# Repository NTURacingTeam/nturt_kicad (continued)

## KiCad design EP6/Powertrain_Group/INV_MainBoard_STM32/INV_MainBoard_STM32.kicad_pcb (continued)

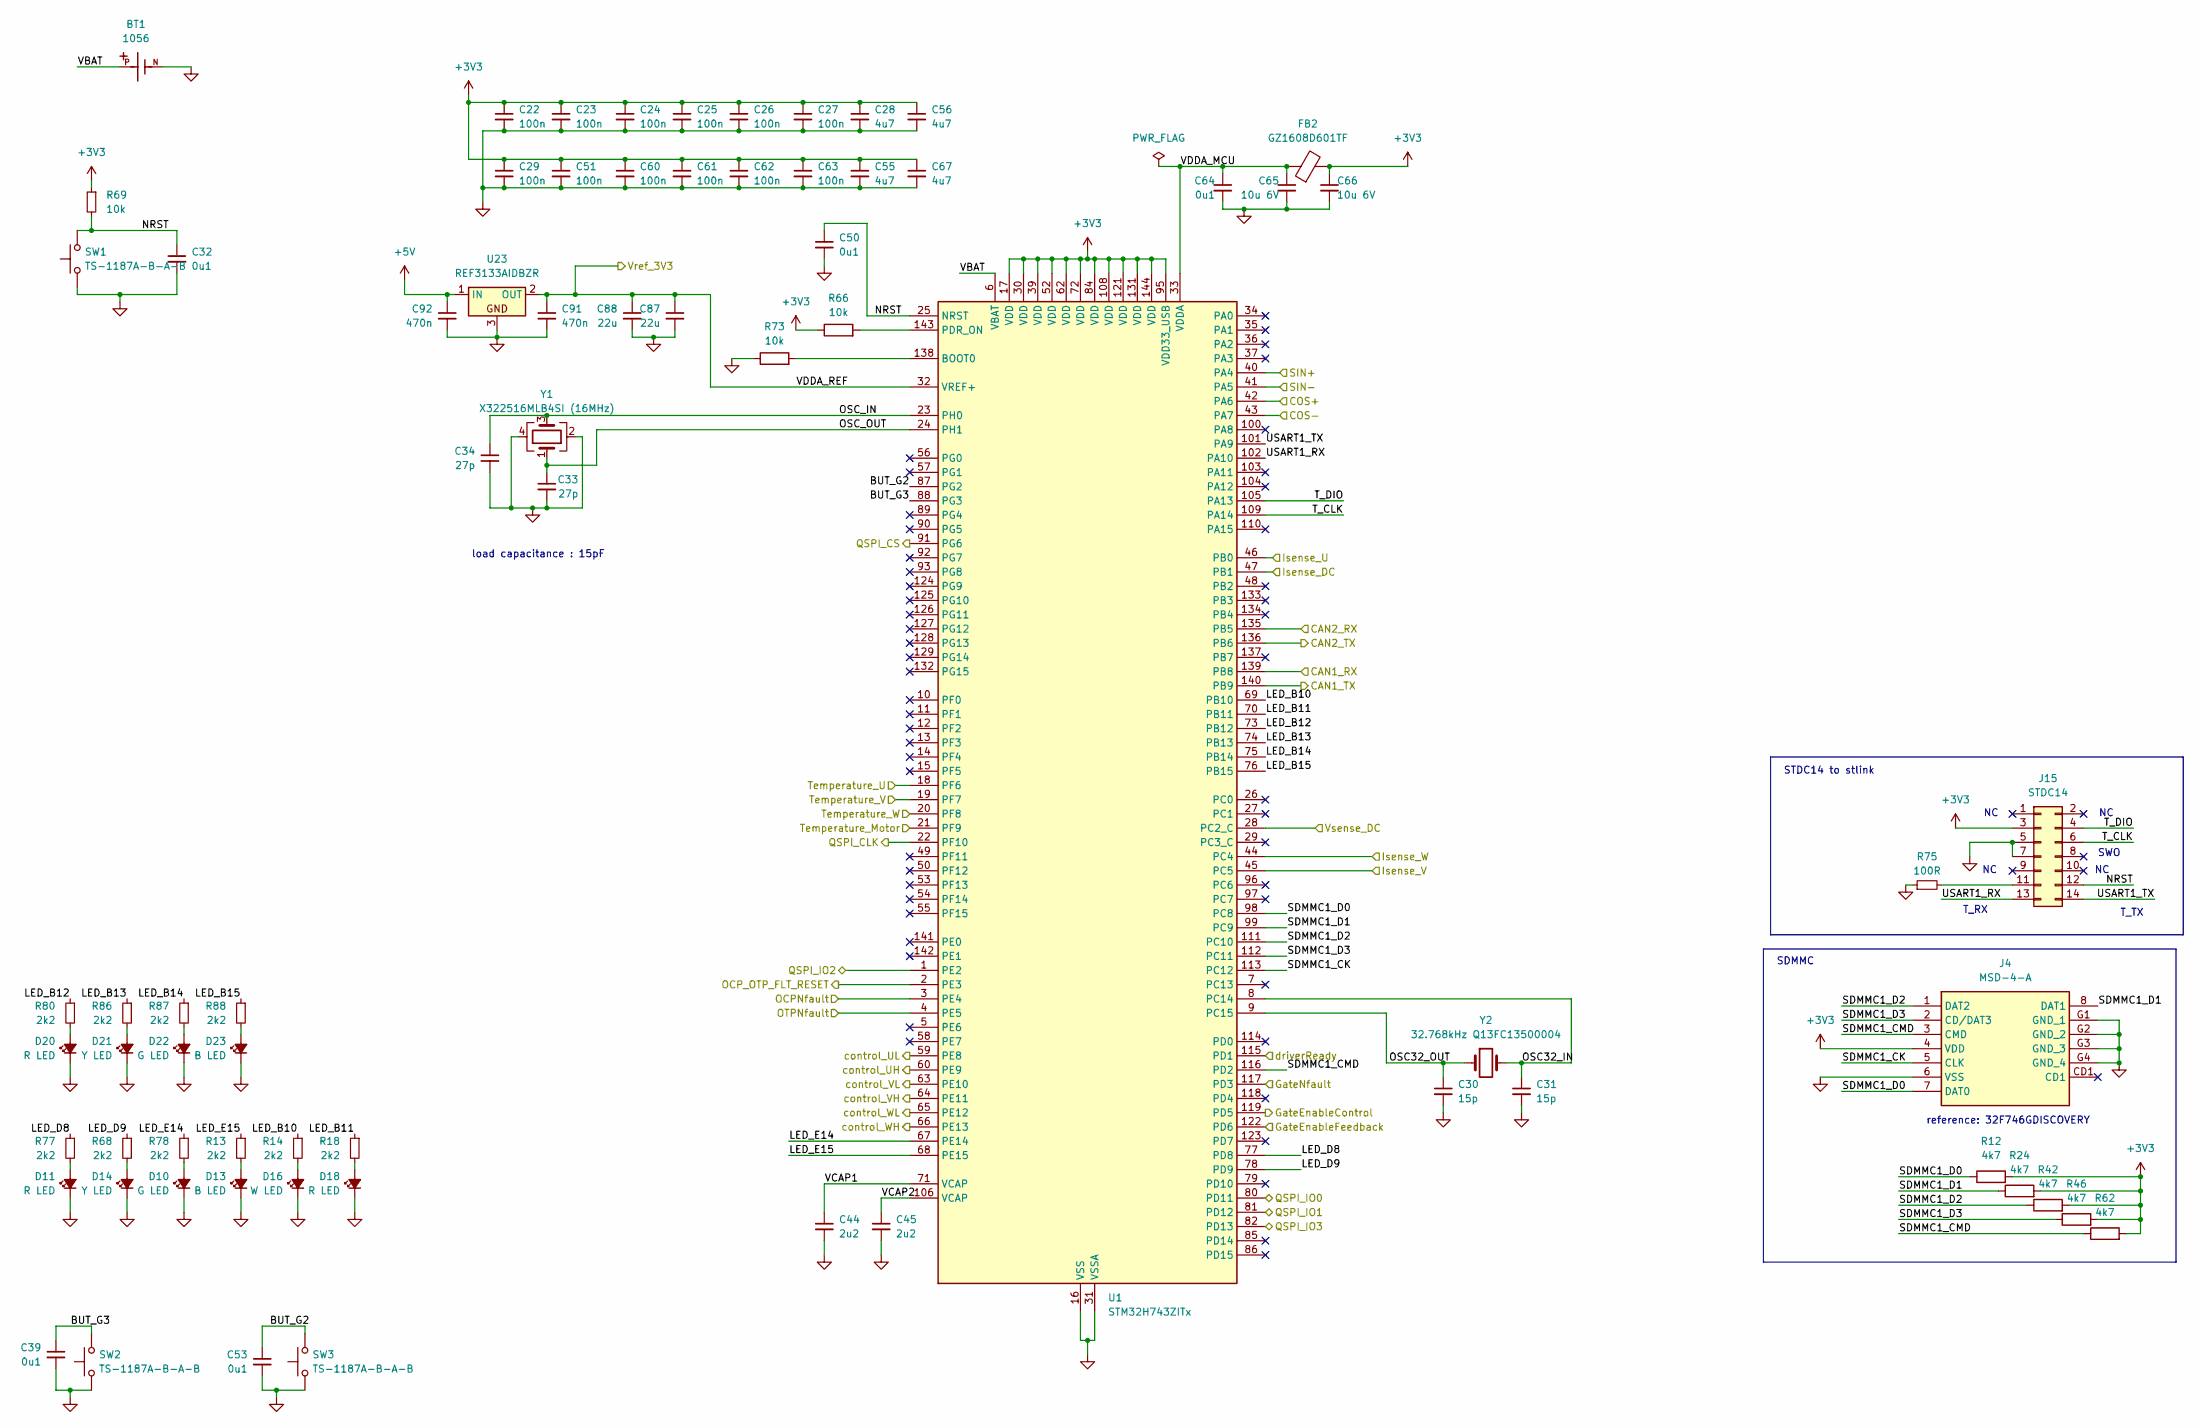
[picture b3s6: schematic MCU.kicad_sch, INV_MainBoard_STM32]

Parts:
BT1: 1056; BAT_1056; PARTREV D
C22, C23, C24, C25, C26, C27, C29, C51, C60, C61, C62, C63: 100n; C_0402_1005Metric
C28, C55, C56, C67: 4u7; C_0402_1005Metric
C30, C31: 15p; C_0402_1005Metric
C32, C39, C50, C53, C64: 0u1; C_0402_1005Metric
C33, C34: 27p; C_0402_1005Metric
C44, C45: 2u2; C_0402_1005Metric
C65, C66: 10u 6V; C_0402_1005Metric
C87, C88: 22u; C_0805_2012Metric
C91, C92: 470n; C_0603_1608Metric
D10, D22: G LED; LED_0603_1608Metric
D11, D18, D20: R LED; LED_0603_1608Metric
D13, D23: B LED; LED_0603_1608Metric
D14, D21: Y LED; LED_0603_1608Metric
D16: W LED; LED_0603_1608Metric
FB2: GZ1608D601TF; C_0603_1608Metric
J4: MSD-4-A; MSD4A; Mouser Part Number 179-MSD-4-A
J15: STDC14; box_header_14P_pitch127
R12, R24, R42, R46, R62: 4k7; R_0402_1005Metric
R13, R14, R18, R68, R77, R78, R80, R86, R87, R88: 2k2; R_0402_1005Metric
R66, R69, R73: 10k; R_0402_1005Metric
R75: 100R; R_0402_1005Metric
SW1, SW2, SW3: TS-1187A-B-A-B; SW_SPST_TL3342
U1: STM32H743ZITx; LQFP-144_20x20mm_P0.5mm
U23: REF3133AIDBZR; SOT-23
Y1: X322516MLB4SI (16MHz); Crystal_SMD_3225-4Pin_3.2x2.5mm
Y2: 32.768kHz Q13FC13500004; Crystal_SMD_3215-2Pin_3.2x1.5mm

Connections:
+3V3: C22.1, C23.1, C24.1, C25.1, C26.1, C27.1, C28.1, C29.1, C51.1, C55.1, C56.1, C60.1, C61.1, C62.1, C63.1, C66.1, C67.1, FB2.2, J4.4 (VDD), J15.3, R12.2, R24.2, R42.2, R46.2, R62.2, R66.1, R69.1, U1.17 (VDD), U1.30 (VDD), U1.39 (VDD), U1.52 (VDD), U1.62 (VDD), U1.72 (VDD), U1.84 (VDD), U1.95 (VDD33_USB), U1.108 (VDD), U1.121 (VDD), U1.131 (VDD), U1.144 (VDD); also elsewhere on the board
+5V: C92.1, U23.1 (IN); also elsewhere on the board
/EncoderDifVconverter/cos+3V3_out: U1.42 (PA6); also elsewhere on the board
/EncoderDifVconverter/cos-3V3_out: U1.43 (PA7); also elsewhere on the board
/EncoderDifVconverter/sin+3V3_out: U1.40 (PA4); also elsewhere on the board
/EncoderDifVconverter/sin-3V3_out: U1.41 (PA5); also elsewhere on the board
/FLTN: U1.117 (PD3); also elsewhere on the board
/GATE_EN: U1.122 (PD6); also elsewhere on the board
/GATE_ENC: U1.119 (PD5); also elsewhere on the board
/Isense&motT_OCP&OTP/FLT_LATCH_RESET: U1.2 (PE3); also elsewhere on the board
/Isense&motT_OCP&OTP/Isense_DC: U1.47 (PB1); also elsewhere on the board
/Isense&motT_OCP&OTP/Isense_U: U1.46 (PB0); also elsewhere on the board
/Isense&motT_OCP&OTP/Isense_V: U1.45 (PC5); also elsewhere on the board
/Isense&motT_OCP&OTP/Isense_W: U1.44 (PC4); also elsewhere on the board
/Isense&motT_OCP&OTP/OCP_SENSE: U1.3 (PE4); also elsewhere on the board
/Isense&motT_OCP&OTP/OTP_SENSE: U1.4 (PE5); also elsewhere on the board
/MCU/BUT_G2: C53.1, SW3.2, U1.87 (PG2)
/MCU/BUT_G3: C39.1, SW2.2, U1.88 (PG3)
/MCU/CAN1_RX: U1.139 (PB8); also elsewhere on the board
/MCU/CAN1_TX: U1.140 (PB9); also elsewhere on the board
/MCU/CAN2_RX: U1.135 (PB5); also elsewhere on the board
/MCU/CAN2_TX: U1.136 (PB6); also elsewhere on the board
/MCU/LED_B10: R14.1, U1.69 (PB10)
/MCU/LED_B11: R18.1, U1.70 (PB11)
/MCU/LED_B12: R80.1, U1.73 (PB12)
/MCU/LED_B13: R86.1, U1.74 (PB13)
/MCU/LED_B14: R87.1, U1.75 (PB14)
/MCU/LED_B15: R88.1, U1.76 (PB15)
/MCU/LED_D8: R77.1, U1.77 (PD8)
/MCU/LED_D9: R68.1, U1.78 (PD9)
/MCU/LED_E14: R78.1, U1.67 (PE14)
/MCU/LED_E15: R13.1, U1.68 (PE15)
/MCU/NRST: C32.1, C50.1, J15.12, R69.2, SW1.2, U1.25 (NRST)
/MCU/OSC32_IN: C31.1, U1.8 (PC14), Y2.2
/MCU/OSC32_OUT: C30.1, U1.9 (PC15), Y2.1
/MCU/OSC_IN: C34.1, U1.23 (PH0), Y1.3
/MCU/OSC_OUT: C33.1, U1.24 (PH1), Y1.1
/MCU/QSPI_CLK: U1.22 (PF10); also elsewhere on the board
/MCU/QSPI_CS: U1.91 (PG6); also elsewhere on the board
/MCU/QSPI_IO0: U1.80 (PD11); also elsewhere on the board
/MCU/QSPI_IO1: U1.81 (PD12); also elsewhere on the board
/MCU/QSPI_IO2: U1.1 (PE2); also elsewhere on the board
/MCU/QSPI_IO3: U1.82 (PD13); also elsewhere on the board
/MCU/SDMMC1_CK: J4.5 (CLK), U1.113 (PC12)
/MCU/SDMMC1_CMD: J4.3 (CMD), R62.1, U1.116 (PD2)
/MCU/SDMMC1_D0: J4.7 (DAT0), R12.1, U1.98 (PC8)
/MCU/SDMMC1_D1: J4.8 (DAT1), R24.1, U1.99 (PC9)
/MCU/SDMMC1_D2: J4.1 (DAT2), R42.1, U1.111 (PC10)
/MCU/SDMMC1_D3: J4.2 (CD/DAT3), R46.1, U1.112 (PC11)
/MCU/T_CLK: J15.6, U1.109 (PA14)
/MCU/T_DIO: J15.4, U1.105 (PA13)
/MCU/USART1_RX: J15.13, U1.102 (PA10)
/MCU/USART1_TX: J15.14, U1.101 (PA9)
/MCU/VBAT: BT1.P, U1.6 (VBAT)
/MCU/VCAP1: C44.1, U1.71 (VCAP)
/MCU/VCAP2: C45.1, U1.106 (VCAP)
/MCU/VDDA_MCU: C64.1, C65.1, FB2.1, U1.33 (VDDA)
/MCU/VDDA_REF: C87.1, C88.1, C91.1, U1.32 (VREF+), U23.2 (OUT); also elsewhere on the board
/RDY: U1.115 (PD1); also elsewhere on the board
/T_filt_U: U1.18 (PF6); also elsewhere on the board
/T_filt_V: U1.19 (PF7); also elsewhere on the board
/T_filt_W: U1.20 (PF8); also elsewhere on the board
/T_filt_mot: U1.21 (PF9); also elsewhere on the board
/UH: U1.60 (PE9); also elsewhere on the board
/UL: U1.59 (PE8); also elsewhere on the board
/VH: U1.64 (PE11); also elsewhere on the board
/VL: U1.63 (PE10); also elsewhere on the board
/Vsense_filt_DC: U1.28 (PC2_C); also elsewhere on the board
/WH: U1.66 (PE13); also elsewhere on the board
/WL: U1.65 (PE12); also elsewhere on the board
GND: BT1.N, C22.2, C23.2, C24.2, C25.2, C26.2, C27.2, C28.2, C29.2, C30.2, C31.2, C32.2, C33.2, C34.2, C39.2, C44.2, C45.2, C50.2, C51.2, C53.2, C55.2, C56.2, C60.2, C61.2, C62.2, C63.2, C64.2, C65.2, C66.2, C67.2, C87.2, C88.2, C91.2, C92.2, D10.1 (K), D11.1 (K), D13.1 (K), D14.1 (K), D16.1 (K), D18.1 (K), D20.1 (K), D21.1 (K), D22.1 (K), D23.1 (K), J4.6 (VSS), J4.G1 (GND_1), J4.G2 (GND_2), J4.G3 (GND_3), J4.G4 (GND_4), J15.5, J15.7, R73.1, R75.1, SW1.1, SW2.1, SW3.1, U1.16 (VSS), U1.31 (VSSA), U1.38 (VSS), U1.51 (VSS), U1.61 (VSS), U1.83 (VSS), U1.94 (VSS), U1.107 (VSS), U1.120 (VSS), U1.130 (VSS), U23.3, Y1.2, Y1.4; also elsewhere on the board
unnamed: D10.2 (A), R78.2
unnamed: D11.2 (A), R77.2
unnamed: D13.2 (A), R13.2
unnamed: D14.2 (A), R68.2
unnamed: D16.2 (A), R14.2
unnamed: D18.2 (A), R18.2
unnamed: D20.2 (A), R80.2
unnamed: D21.2 (A), R86.2
unnamed: D22.2 (A), R87.2
unnamed: D23.2 (A), R88.2
unnamed: J15.11, R75.2
unnamed: R73.2, U1.138 (BOOT0)
unnamed: R66.2, U1.143 (PDR_ON)

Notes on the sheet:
reference: 32F746GDISCOVERY
T_TX
load capacitance : 15pF
SDMMC
STDC14 to stlink
T_RX
SWO

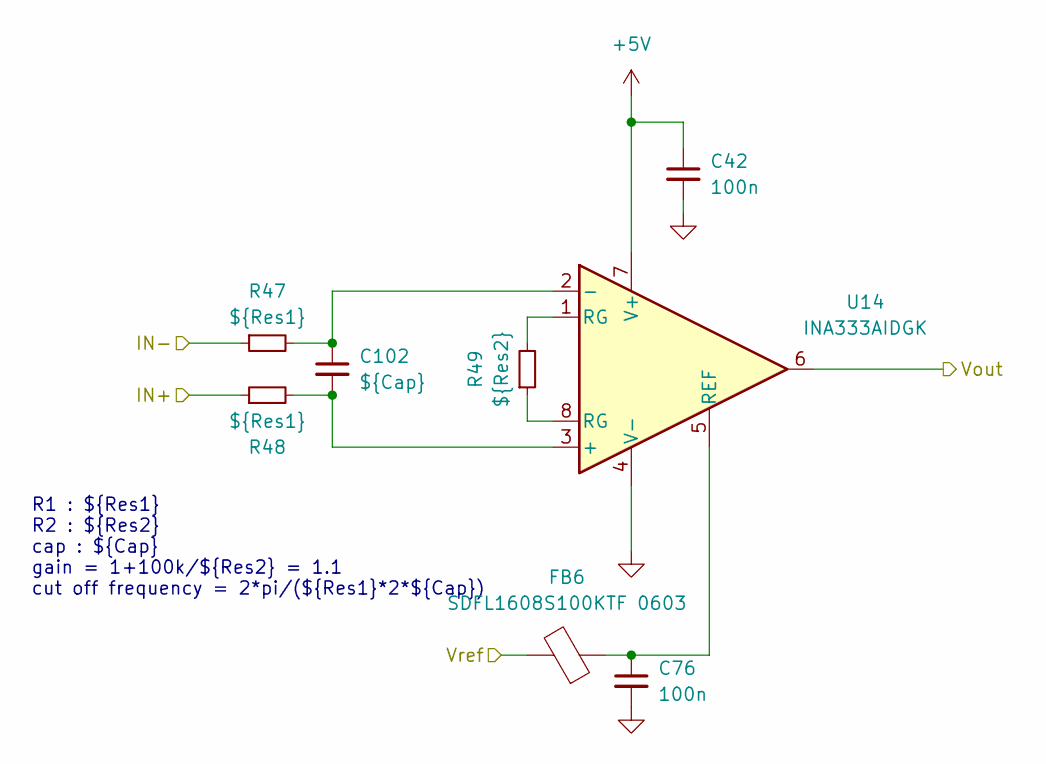
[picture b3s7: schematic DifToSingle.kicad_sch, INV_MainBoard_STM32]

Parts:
C42, C76: 100n; C_0402_1005Metric
C102: ${Cap}; C_0402_1005Metric
FB6: SDFL1608S100KTF 0603; C_0603_1608Metric
R47, R48: ${Res1}; R_0402_1005Metric
R49: ${Res2}; R_0402_1005Metric
U14: INA333AIDGK; MSOP-8_3x3mm_P0.65mm

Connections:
+5V: C42.1, U14.7 (V+); also elsewhere on the board
/Isense&motT_OCP&OTP/Isense_W: U14.6; also elsewhere on the board
/Isense&motT_OCP&OTP/Vref_1.65V: FB6.2; also elsewhere on the board
/Isense&motT_OCP&OTP/W+: R47.1; also elsewhere on the board
/Isense&motT_OCP&OTP/W-: R48.1; also elsewhere on the board
GND: C42.2, C76.2, U14.4 (V-); also elsewhere on the board
unnamed: R49.1, U14.8 (RG)
unnamed: R49.2, U14.1 (RG)
unnamed: C102.2, R48.2, U14.3 (+)
unnamed: C102.1, R47.2, U14.2 (-)
unnamed: C76.1, FB6.1, U14.5 (REF)

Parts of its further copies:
C21, C40, C41, C43, C72, C73, C74, C75: 100n; C_0402_1005Metric
FB1, FB3, FB4, FB5: SDFL1608S100KTF 0603; C_0603_1608Metric
U3, U7, U8, U9: INA333AIDGK; MSOP-8_3x3mm_P0.65mm

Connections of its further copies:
+5V: C21.1, C40.1, C41.1, C43.1, U3.7 (V+), U7.7 (V+), U8.7 (V+), U9.7 (V+); also elsewhere on the board
/Isense&motT_OCP&OTP/Isense_DC: U7.6; also elsewhere on the board
/Isense&motT_OCP&OTP/Isense_U: U8.6; also elsewhere on the board
/Isense&motT_OCP&OTP/Isense_V: U9.6; also elsewhere on the board
/Isense&motT_OCP&OTP/Vref_1.65V: FB3.2, FB4.2, FB5.2; also elsewhere on the board
/T_mot: U3.6; also elsewhere on the board
GND: C21.2, C40.2, C41.2, C43.2, C72.2, C73.2, C74.2, C75.2, FB1.2, U3.4 (V-), U7.4 (V-), U8.4 (V-), U9.4 (V-); also elsewhere on the board
unnamed 138: U7.8 (RG); also elsewhere on the board
unnamed 139: U7.1 (RG); also elsewhere on the board
unnamed 140: U8.8 (RG); also elsewhere on the board
unnamed 141: U8.1 (RG); also elsewhere on the board
unnamed 142: U9.8 (RG); also elsewhere on the board
unnamed 143: U9.1 (RG); also elsewhere on the board
unnamed 146: U3.8 (RG); also elsewhere on the board
unnamed 147: U3.1 (RG); also elsewhere on the board
unnamed 153: U3.3 (+); also elsewhere on the board
unnamed 154: U3.2 (-); also elsewhere on the board
unnamed: C72.1, FB1.1, U3.5 (REF)
unnamed 167: U7.3 (+); also elsewhere on the board
unnamed 168: U7.2 (-); also elsewhere on the board
unnamed: C73.1, FB3.1, U7.5 (REF)
unnamed 170: U8.3 (+); also elsewhere on the board
unnamed 171: U8.2 (-); also elsewhere on the board
unnamed: C74.1, FB4.1, U8.5 (REF)
unnamed 173: U9.3 (+); also elsewhere on the board
unnamed 174: U9.2 (-); also elsewhere on the board
unnamed: C75.1, FB5.1, U9.5 (REF)

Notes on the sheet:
R1 : ${Res1} R2 : ${Res2} cap : ${Cap} gain = 1+100k/${Res2} = 1.1 cut off frequency = 2*pi/(${Res1}*2*${Cap})

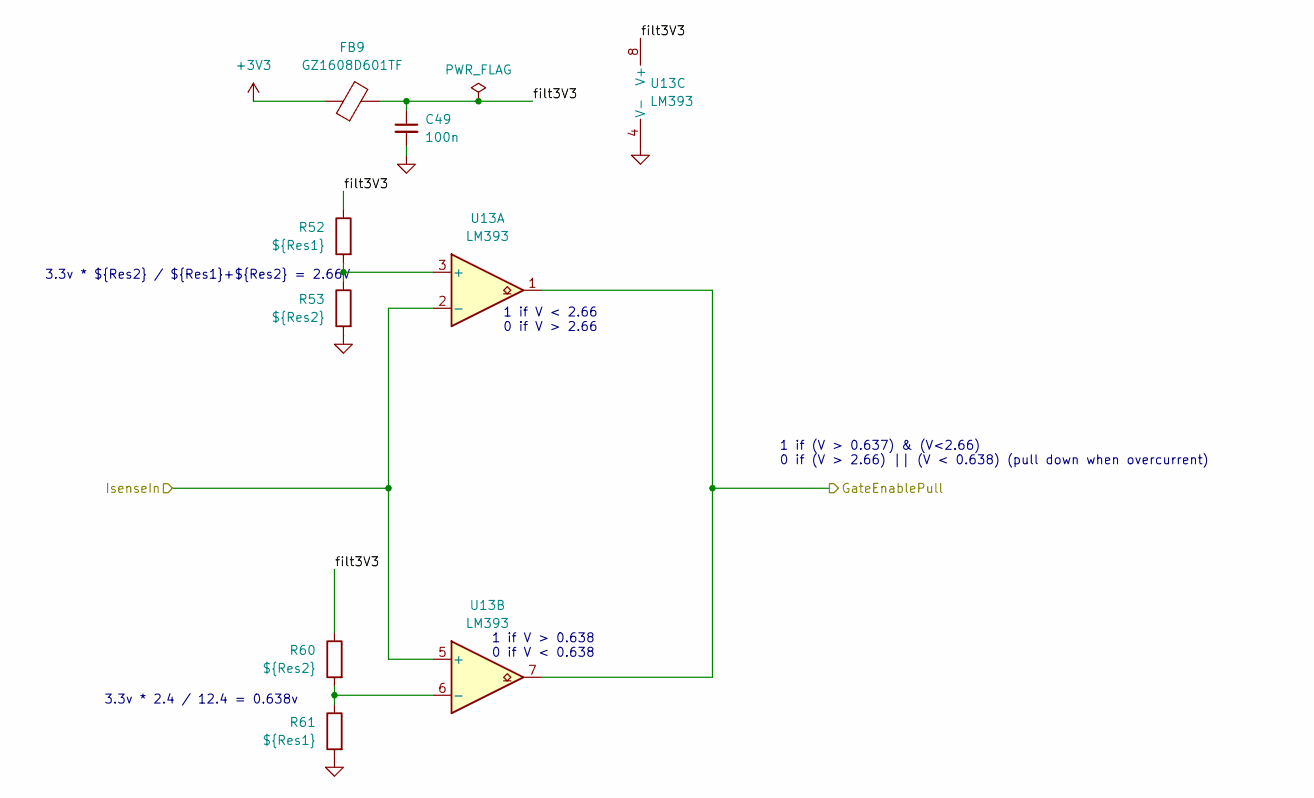
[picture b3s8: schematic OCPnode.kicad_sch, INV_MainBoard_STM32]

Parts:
C49: 100n; C_0402_1005Metric
FB9: GZ1608D601TF; C_0603_1608Metric
R52, R61: ${Res1}; R_0402_1005Metric
R53, R60: ${Res2}; R_0402_1005Metric
U13: LM393; SOIC-8_3.9x4.9mm_P1.27mm

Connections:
+3V3: FB9.1; also elsewhere on the board
/Isense&motT_OCP&OTP/OCPnode1/GateEnablePull: U13.1, U13.7; also elsewhere on the board
/Isense&motT_OCP&OTP/OCPnode3/IsenseIn: U13.2 (-), U13.5 (+); also elsewhere on the board
/Isense&motT_OCP&OTP/OCPnode3/filt3V3: C49.1, FB9.2, R52.1, R60.1, U13.8 (V+)
GND: C49.2, R53.2, R61.2, U13.4 (V-); also elsewhere on the board
unnamed: R52.2, R53.1, U13.3 (+)
unnamed: R60.2, R61.1, U13.6 (-)

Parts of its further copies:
C47, C48: 100n; C_0402_1005Metric
FB7, FB8: GZ1608D601TF; C_0603_1608Metric
U11, U12: LM393; SOIC-8_3.9x4.9mm_P1.27mm

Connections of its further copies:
+3V3: FB7.1, FB8.1; also elsewhere on the board
/Isense&motT_OCP&OTP/OCPnode1/GateEnablePull: U11.1, U11.7, U12.1, U12.7; also elsewhere on the board
/Isense&motT_OCP&OTP/OCPnode1/IsenseIn: U11.2 (-), U11.5 (+); also elsewhere on the board
/Isense&motT_OCP&OTP/OCPnode1/filt3V3: C47.1, FB7.2, U11.8 (V+); also elsewhere on the board
/Isense&motT_OCP&OTP/OCPnode2/IsenseIn: U12.2 (-), U12.5 (+); also elsewhere on the board
/Isense&motT_OCP&OTP/OCPnode2/filt3V3: C48.1, FB8.2, U12.8 (V+); also elsewhere on the board
GND: C47.2, C48.2, U11.4 (V-), U12.4 (V-); also elsewhere on the board
unnamed 176: U11.3 (+); also elsewhere on the board
unnamed 177: U11.6 (-); also elsewhere on the board
unnamed 178: U12.3 (+); also elsewhere on the board
unnamed 179: U12.6 (-); also elsewhere on the board

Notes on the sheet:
1 if V < 2.66 0 if V > 2.66
1 if (V > 0.637) & (V<2.66) 0 if (V > 2.66) || (V < 0.638) (pull down when overcurrent)
3.3v * ${Res2} / ${Res1}+${Res2} = 2.66V
3.3v * 2.4 / 12.4 = 0.638v
1 if V > 0.638 0 if V < 0.638

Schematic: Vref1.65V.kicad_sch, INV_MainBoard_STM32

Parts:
C103, C104: 100n; C_0402_1005Metric
R25, R26: 10k; R_0402_1005Metric
U18: NE5532; SOIC-8_3.9x4.9mm_P1.27mm

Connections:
/Isense&motT_OCP&OTP/Vref_1.65V: U18.1, U18.2 (-); also elsewhere on the board
/MCU/VDDA_REF: C103.1, R25.1, U18.8 (V+); also elsewhere on the board
GND: C103.2, C104.2, R26.2, U18.4 (V-); also elsewhere on the board
unnamed: C104.1, R25.2, R26.1, U18.3 (+)

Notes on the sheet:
this was changed to MCP6002 not sure why, checking why
create 1.65V Vref

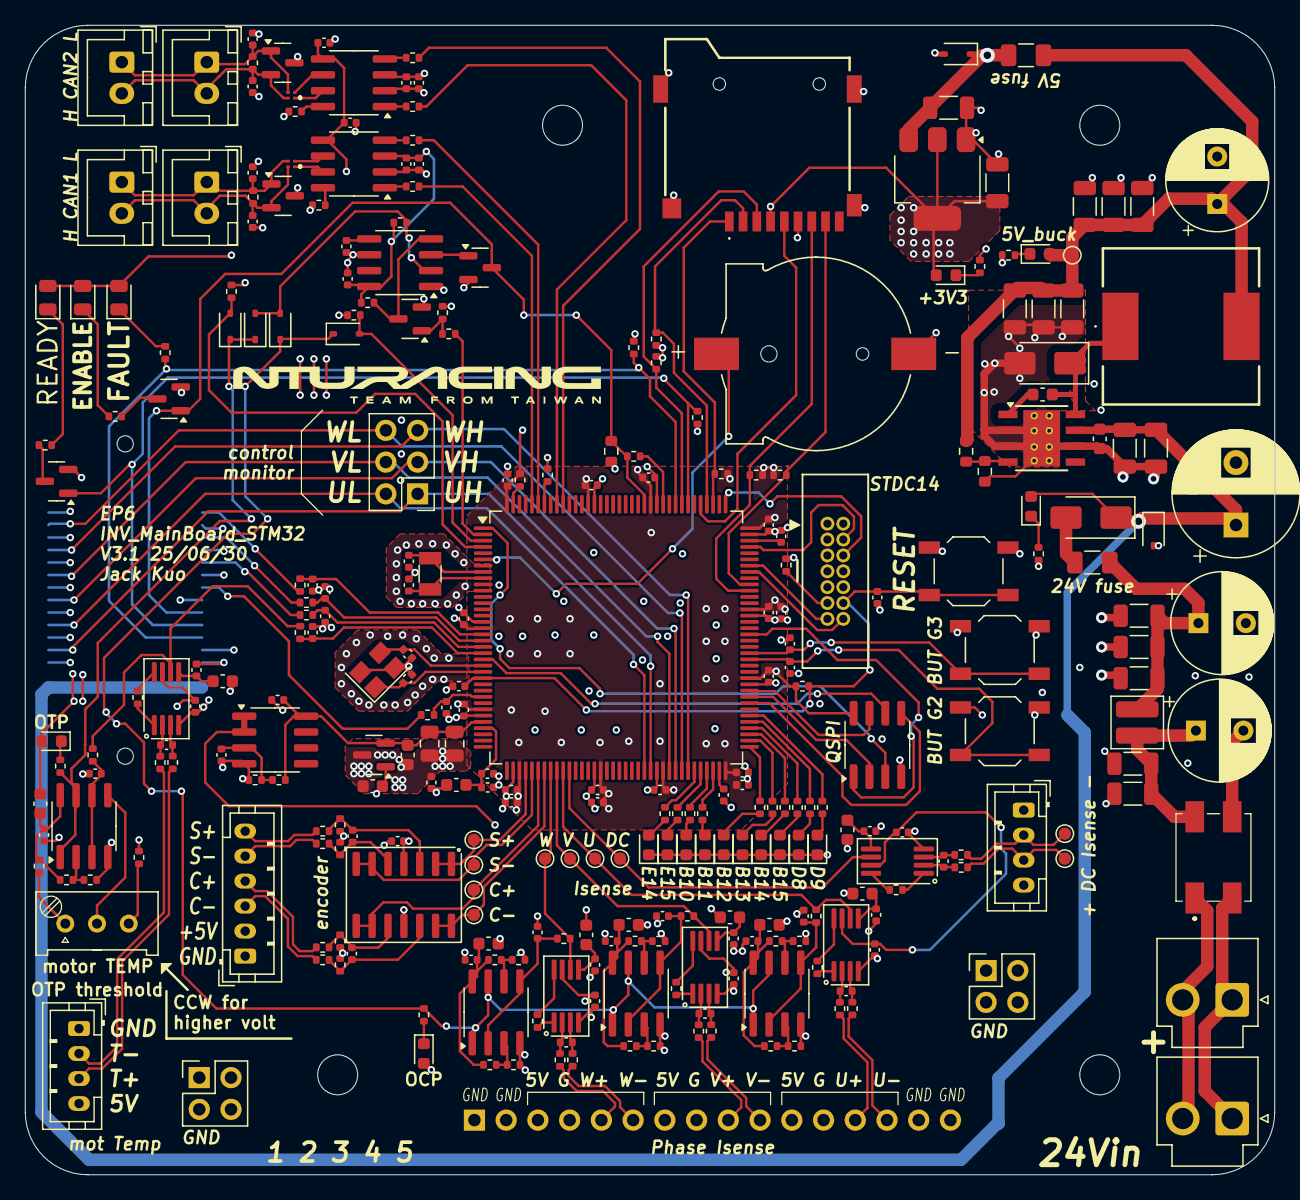
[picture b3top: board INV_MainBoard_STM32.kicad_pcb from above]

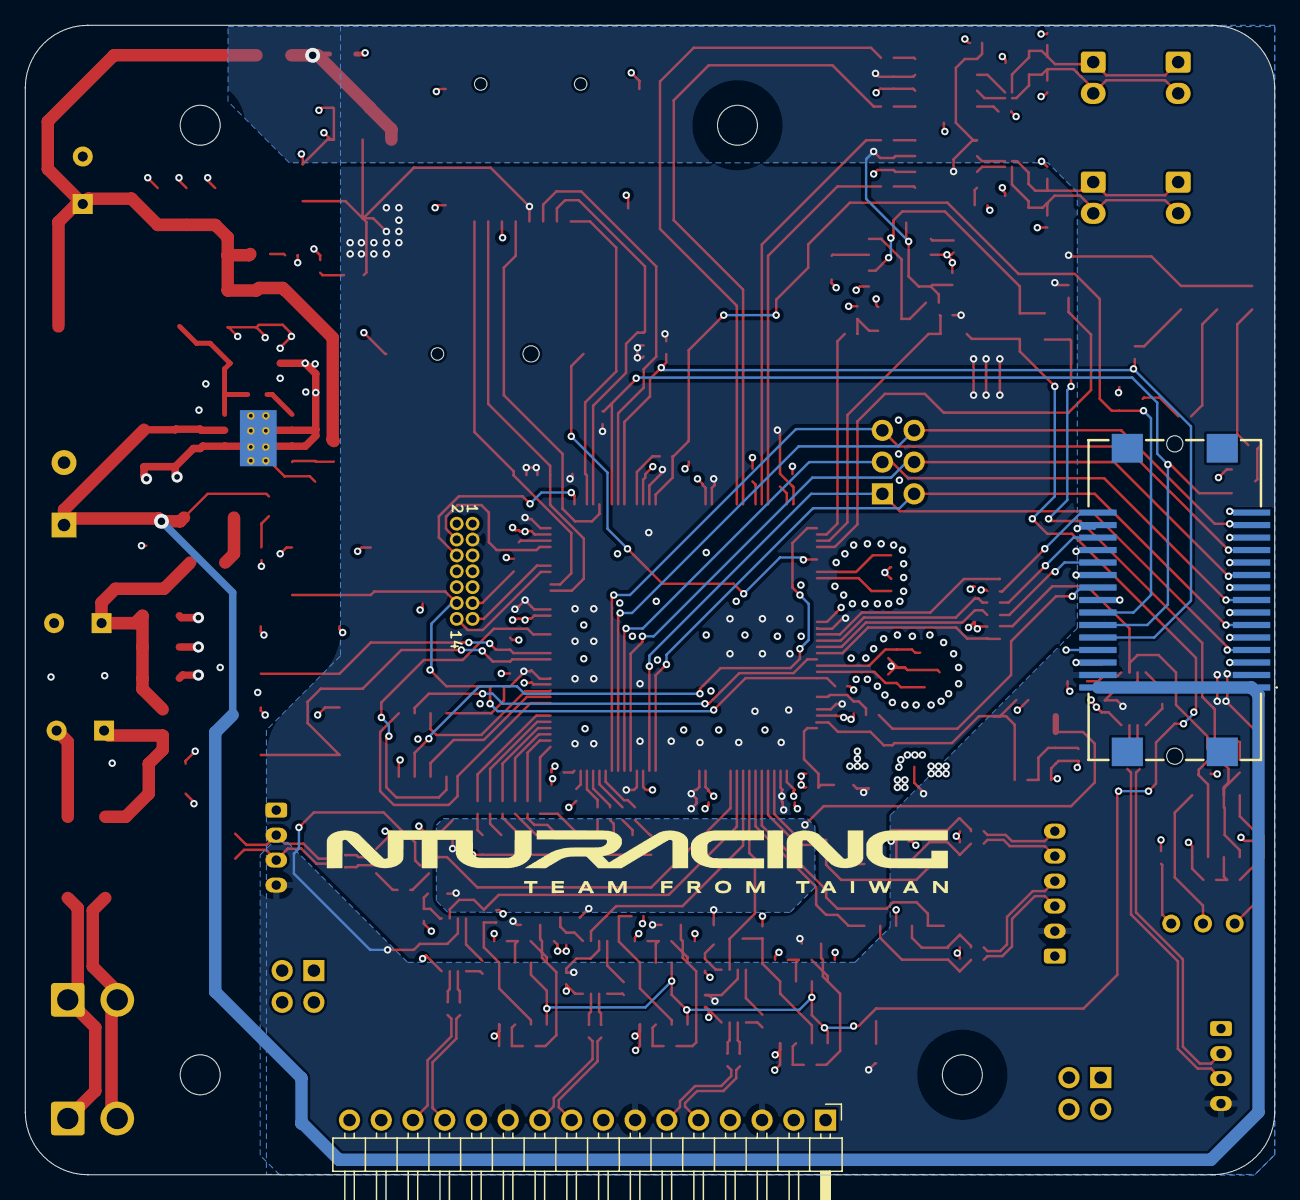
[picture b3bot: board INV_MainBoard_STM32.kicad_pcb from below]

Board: 4 copper layers, 100.0 x 92.0 mm, 302 parts (2 on the bottom side), 193 nets.

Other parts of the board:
C96: 1u; C_0402_1005Metric
C99, C100, C101: 680p; C_0402_1005Metric
R31, R50, R57, R59, R63, R64: 10k; R_0402_1005Metric
R33, R51, R56, R58: 27k; R_0402_1005Metric
R35, R36, R39, R40, R43, R44: 100R; R_0402_1005Metric
R37: 10M; R_0402_1005Metric
R41, R45: 1M; R_0402_1005Metric
R65: 100k; R_0402_1005Metric

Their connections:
/Isense&motT_OCP&OTP/IsenseNode/IN+: R36.1; also elsewhere on the board
/Isense&motT_OCP&OTP/IsenseNode/IN-: R35.1; also elsewhere on the board
/Isense&motT_OCP&OTP/MotTempNode/IN+: R64.1; also elsewhere on the board
/Isense&motT_OCP&OTP/MotTempNode/IN-: R63.1; also elsewhere on the board
/Isense&motT_OCP&OTP/OCPnode1/filt3V3: R31.1, R56.1; also elsewhere on the board
/Isense&motT_OCP&OTP/OCPnode2/filt3V3: R50.1, R58.1; also elsewhere on the board
/Isense&motT_OCP&OTP/U+: R39.1; also elsewhere on the board
/Isense&motT_OCP&OTP/U-: R40.1; also elsewhere on the board
/Isense&motT_OCP&OTP/V+: R43.1; also elsewhere on the board
/Isense&motT_OCP&OTP/V-: R44.1; also elsewhere on the board
GND: R33.2, R51.2, R57.2, R59.2; also elsewhere on the board
unnamed 138: R37.1; also elsewhere on the board
unnamed 139: R37.2; also elsewhere on the board
unnamed 140: R41.1; also elsewhere on the board
unnamed 141: R41.2; also elsewhere on the board
unnamed 142: R45.1; also elsewhere on the board
unnamed 143: R45.2; also elsewhere on the board
unnamed 146: R65.1; also elsewhere on the board
unnamed 147: R65.2; also elsewhere on the board
unnamed 153: C96.2, R64.2; also elsewhere on the board
unnamed 154: C96.1, R63.2; also elsewhere on the board
unnamed 167: C99.2, R36.2; also elsewhere on the board
unnamed 168: C99.1, R35.2; also elsewhere on the board
unnamed 170: C100.2, R40.2; also elsewhere on the board
unnamed 171: C100.1, R39.2; also elsewhere on the board
unnamed 173: C101.2, R44.2; also elsewhere on the board
unnamed 174: C101.1, R43.2; also elsewhere on the board
unnamed 176: R31.2, R33.1; also elsewhere on the board
unnamed 177: R56.2, R57.1; also elsewhere on the board
unnamed 178: R50.2, R51.1; also elsewhere on the board
unnamed 179: R58.2, R59.1; also elsewhere on the board

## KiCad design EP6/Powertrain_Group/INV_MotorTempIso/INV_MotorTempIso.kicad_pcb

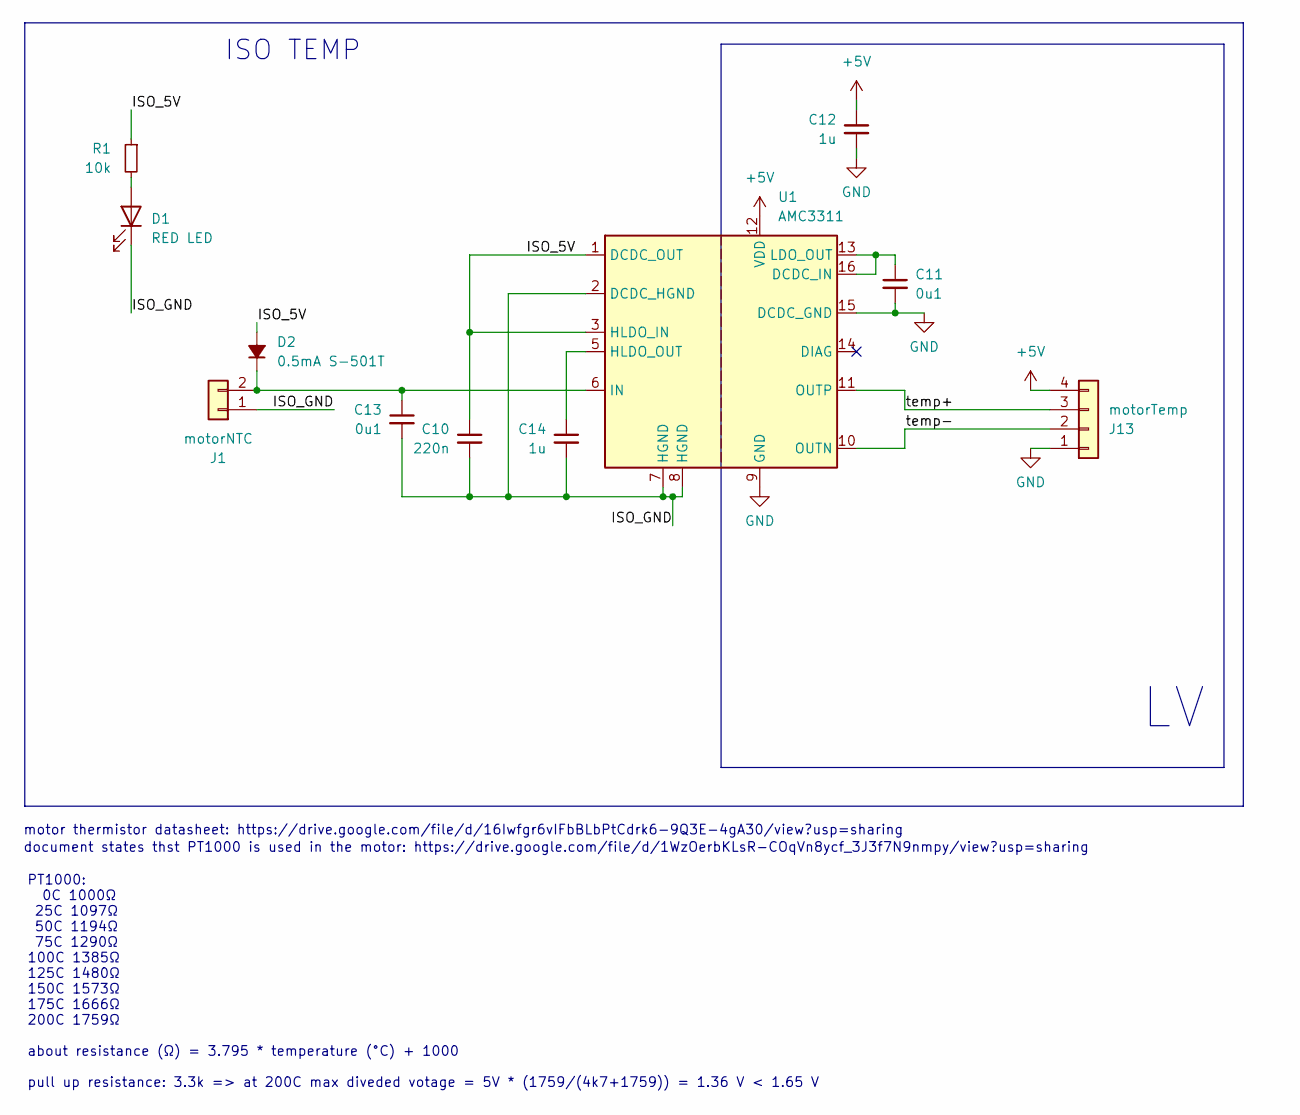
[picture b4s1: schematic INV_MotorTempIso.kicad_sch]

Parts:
C10: 220n; C_0603_1608Metric
C11, C13: 0u1; C_0603_1608Metric
C12, C14: 1u; C_0603_1608Metric
D1: RED LED; LED_0603_1608Metric
D2: 0.5mA S-501T; D_1206_3216Metric
J1: motorNTC; JST_PH_S2B-PH-K_1x02_P2.00mm_Horizontal
J13: motorTemp; JST_PH_S4B-PH-K_1x04_P2.00mm_Horizontal
R1: 10k; R_0603_1608Metric
U1: AMC3311; SOIC-16W_7.5x10.3mm_P1.27mm

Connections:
+5V: C12.1, J13.4, U1.12 (VDD)
/ISO_5V: C10.1, D2.2 (A), R1.1, U1.1 (DCDC_OUT), U1.3 (HLDO_IN)
/ISO_GND: C10.2, C13.2, C14.2, D1.1 (K), J1.1, U1.2 (DCDC_HGND), U1.7 (HGND), U1.8 (HGND)
/temp+: J13.3, U1.11 (OUTP)
/temp-: J13.2, U1.10 (OUTN)
GND: C11.2, C12.2, J13.1, U1.9 (GND), U1.15 (DCDC_GND)
unnamed: D1.2 (A), R1.2
unnamed: C13.1, D2.1 (K), J1.2, U1.6 (IN)
unnamed: C11.1, U1.13 (LDO_OUT), U1.16 (DCDC_IN)
unnamed: C14.1, U1.5 (HLDO_OUT)

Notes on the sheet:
document states thst PT1000 is used in the motor: https://drive.google.com/file/d/1WzOerbKLsR-COqVn8ycf_3J3f7N9nmpy/view?usp=sharing
motor thermistor datasheet: https://drive.google.com/file/d/16Iwfgr6vIFbBLbPtCdrk6-9Q3E-4gA30/view?usp=sharing
PT1000: 0C 1000Ω 25C 1097Ω 50C 1194Ω 75C 1290Ω 100C 1385Ω 125C 1480Ω 150C 1573Ω 175C 1666Ω 200C 1759Ω about resistance (Ω) = 3.795 * temperature (°C) + 1000 pull up resistance: 3.3k => at 200C max diveded votage = 5V * (1759/(4k7+1759)) = 1.36 V < 1.65 V
ISO TEMP

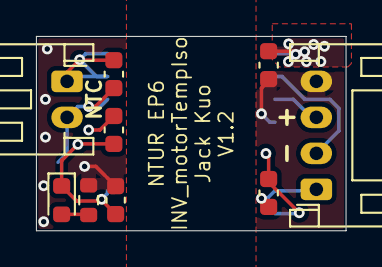
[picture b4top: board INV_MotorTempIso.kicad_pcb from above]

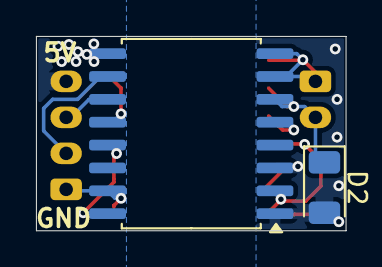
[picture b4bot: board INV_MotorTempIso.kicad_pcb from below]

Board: 4 copper layers, 17.2 x 10.8 mm, 11 parts (2 on the bottom side), 10 nets.

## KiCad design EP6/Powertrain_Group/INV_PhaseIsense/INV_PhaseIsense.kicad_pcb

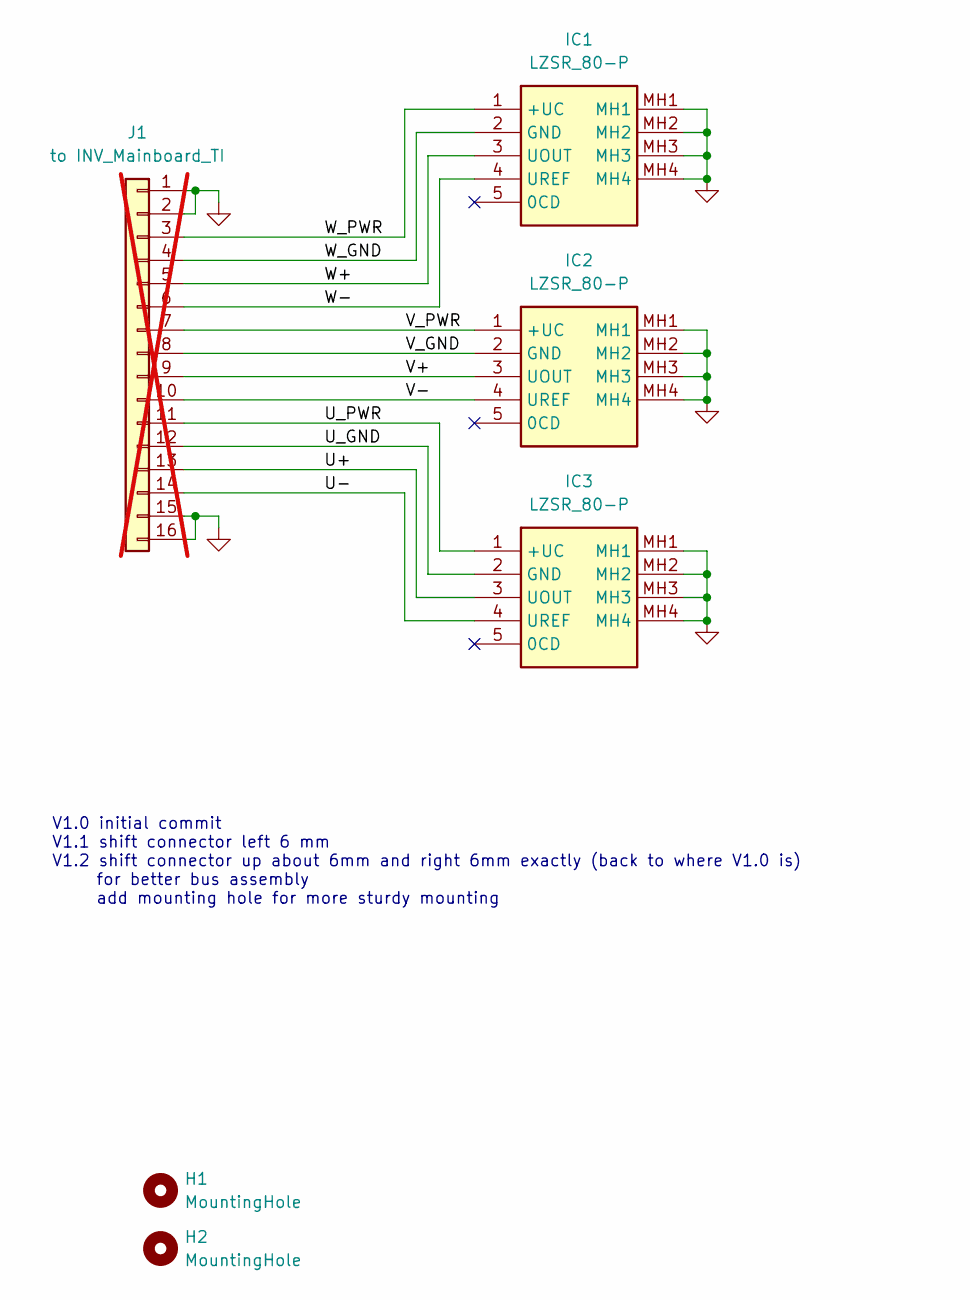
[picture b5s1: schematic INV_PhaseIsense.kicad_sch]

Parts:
H1, H2: MountingHole; MountingHole_3.2mm_M3
IC1, IC2, IC3: LZSR_80-P; LZSR80P; Manufacturer_Part_Number LZSR 80-P
J1: to INV_Mainboard_TI; PinHeader_1x16_P2.54mm_Vertical; not fitted

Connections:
/U+: IC3.3 (UOUT), J1.13
/U-: IC3.4 (UREF), J1.14
/U_GND: IC3.2 (GND), J1.12
/U_PWR: IC3.1 (+UC), J1.11
/V+: IC2.3 (UOUT), J1.9
/V-: IC2.4 (UREF), J1.10
/V_GND: IC2.2 (GND), J1.8
/V_PWR: IC2.1 (+UC), J1.7
/W+: IC1.3 (UOUT), J1.5
/W-: IC1.4 (UREF), J1.6
/W_GND: IC1.2 (GND), J1.4
/W_PWR: IC1.1 (+UC), J1.3
GND: IC1.MH1, IC1.MH2, IC1.MH3, IC1.MH4, IC2.MH1, IC2.MH2, IC2.MH3, IC2.MH4, IC3.MH1, IC3.MH2, IC3.MH3, IC3.MH4, J1.1, J1.2, J1.15, J1.16

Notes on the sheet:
V1.0 initial commit V1.1 shift connector left 6 mm V1.2 shift connector up about 6mm and right 6mm exactly (back to where V1.0 is) for better bus assembly add mounting hole for more sturdy mounting

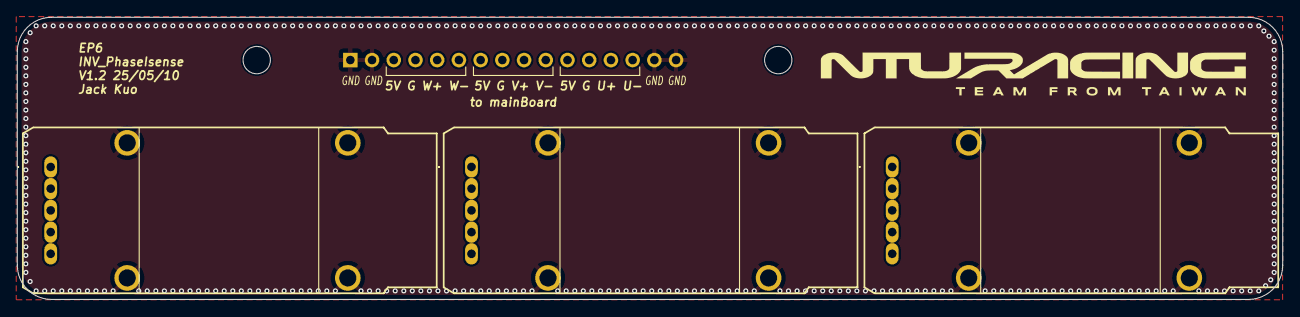
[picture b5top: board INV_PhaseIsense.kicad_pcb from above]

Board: 4 copper layers, 148.0 x 33.0 mm, 6 parts (1 on the bottom side), 13 nets.
